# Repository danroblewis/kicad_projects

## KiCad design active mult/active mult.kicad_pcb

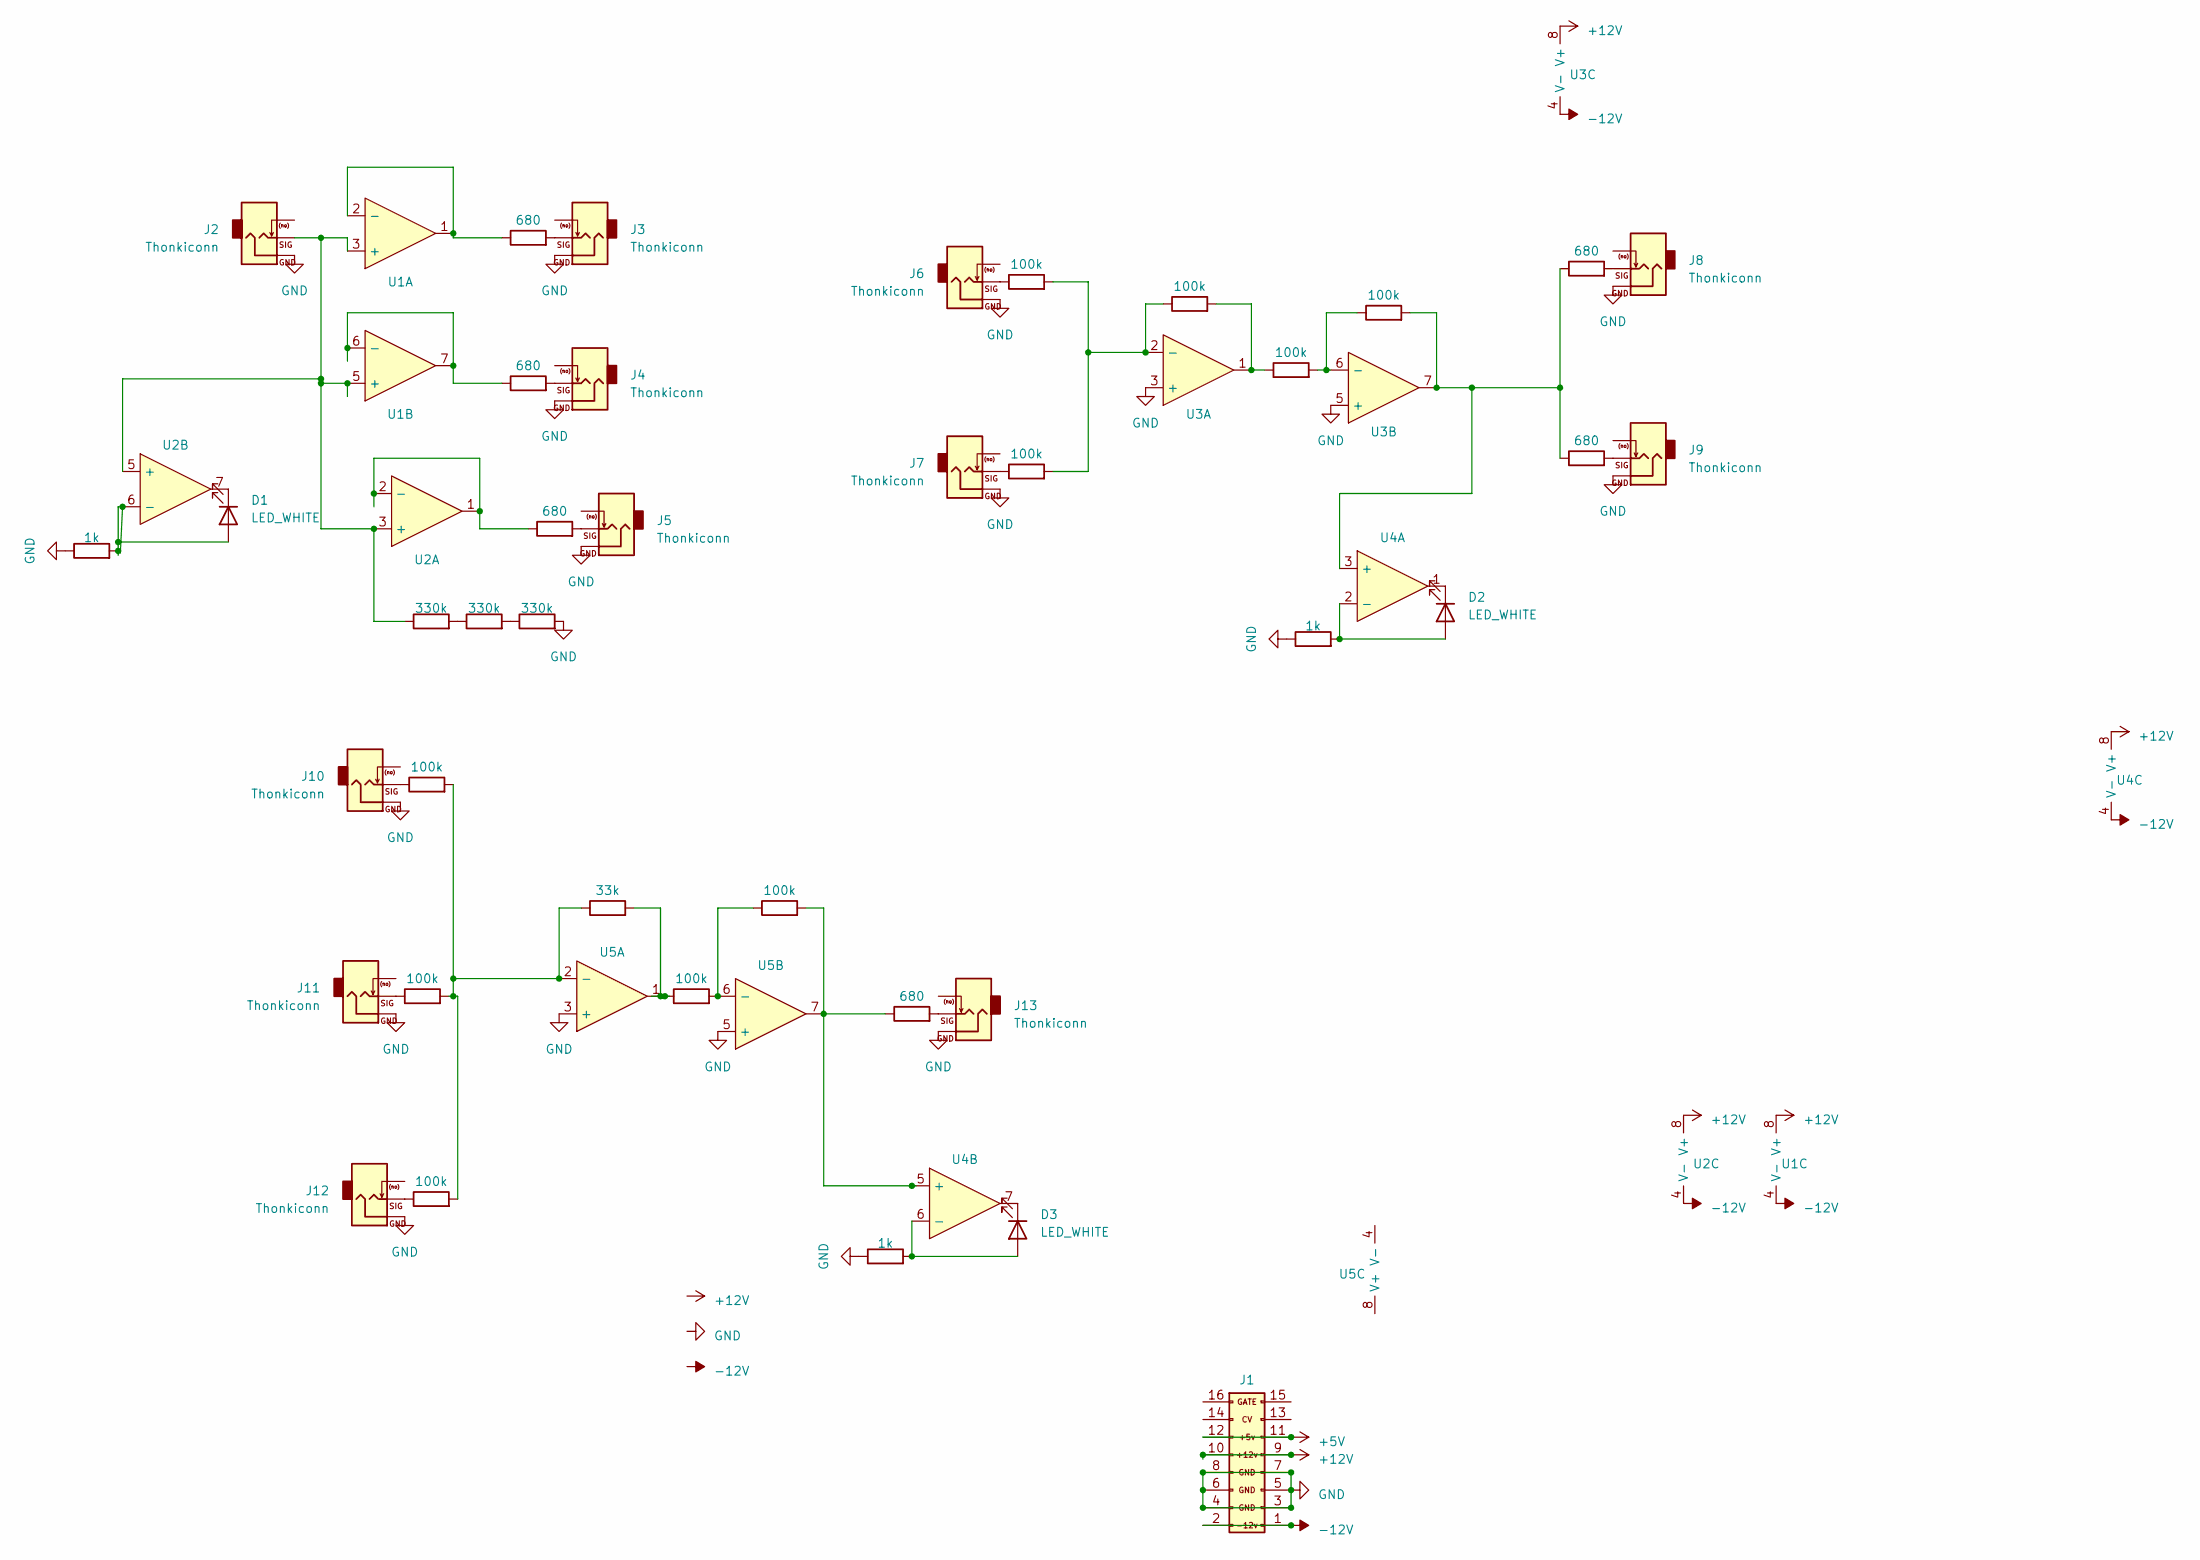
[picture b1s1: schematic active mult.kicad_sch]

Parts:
D1, D2, D3: LED_WHITE; LED_0603_1608Metric; LCSC C2290
J1: EuroPower16; IDC-Header_2x08_P2.54mm_Vertical_SMD; lcsc C383608
J2, J3, J4, J5, J6, J7, J8, J9, J10, J11, J12, J13: Thonkiconn; Jack_3.5mm_QingPu_WQP-PJ398SM_Vertical_CircularHoles
R1, R13, R21: 1k; R_0603_1608Metric; LCSC C21190
R2, R5, R6, R8, R9, R20: 680; R_0603_1608Metric; LCSC C23228
R3, R4, R10, R11, R12, R14, R15, R16, R18, R19: 100k; R_0603_1608Metric; LCSC C25803
R17: 33k; R_0603_1608Metric; LCSC C4216
R22, R23, R24: 330k; R_0603_1608Metric; LCSC C23137
U1, U2, U3, U4, U5: TL072; SOIC-8_3.9x4.9mm_P1.27mm; LCSC C6961

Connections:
+5V: J1.11 (+5v_R), J1.12 (+5v_L)
+12V: J1.9 (+12V_R), J1.10 (+12V_L), U1.8 (V+), U2.8 (V+), U3.8 (V+), U4.8 (V+)
-12V: J1.1 (-12v_R), J1.2 (-12v_L), U1.4 (V-), U2.4 (V-), U3.4 (V-), U4.4 (V-)
GND: J1.3 (GND), J1.4 (GND), J1.5 (GND_R3), J1.6 (GND_L3), J1.7 (GND_R2), J1.8 (GND_L2), J2.S, J3.S, J4.S, J5.S, J6.S, J7.S, J8.S, J9.S, J10.S, J11.S, J12.S, J13.S, R1.1, R13.1, R21.1, R24.2, U3.3 (+), U3.5 (+), U5.3 (+), U5.5 (+)
unnamed: D1.2 (A), R1.2, U2.6 (-)
unnamed: D1.1 (K), U2.7
unnamed: D2.2 (A), R13.2, U4.2 (-)
unnamed: D2.1 (K), U4.1
unnamed: D3.2 (A), R21.2, U4.6 (-)
unnamed: D3.1 (K), U4.7
unnamed: J3.T, R2.2
unnamed: J4.T, R6.2
unnamed: J5.T, R8.2
unnamed: J6.T, R3.1
unnamed: J7.T, R4.1
unnamed: J8.T, R5.2
unnamed: J9.T, R9.2
unnamed: J10.T, R14.1
unnamed: J11.T, R15.1
unnamed: J12.T, R16.1
unnamed: J13.T, R20.2
unnamed: R10.2, R11.1, U3.1
unnamed: R17.2, R18.1, U5.1
unnamed: R22.2, R23.1
unnamed: R23.2, R24.1
unnamed: J2.T, R22.1, U1.3 (+), U1.5 (+), U2.3 (+), U2.5 (+)
unnamed: R2.1, U1.1, U1.2 (-)
unnamed: R6.1, U1.6 (-), U1.7
unnamed: R8.1, U2.1, U2.2 (-)
unnamed: R3.2, R4.2, R10.1, U3.2 (-)
unnamed: R11.2, R12.1, U3.6 (-)
unnamed: R5.1, R9.1, R12.2, U3.7, U4.3 (+)
unnamed: R19.2, R20.1, U4.5 (+), U5.7
unnamed: R14.2, R15.2, R16.2, R17.1, U5.2 (-)
unnamed: R18.2, R19.1, U5.6 (-)

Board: 2 copper layers, 44 parts (12 on the bottom side), 35 nets, no tracks yet.

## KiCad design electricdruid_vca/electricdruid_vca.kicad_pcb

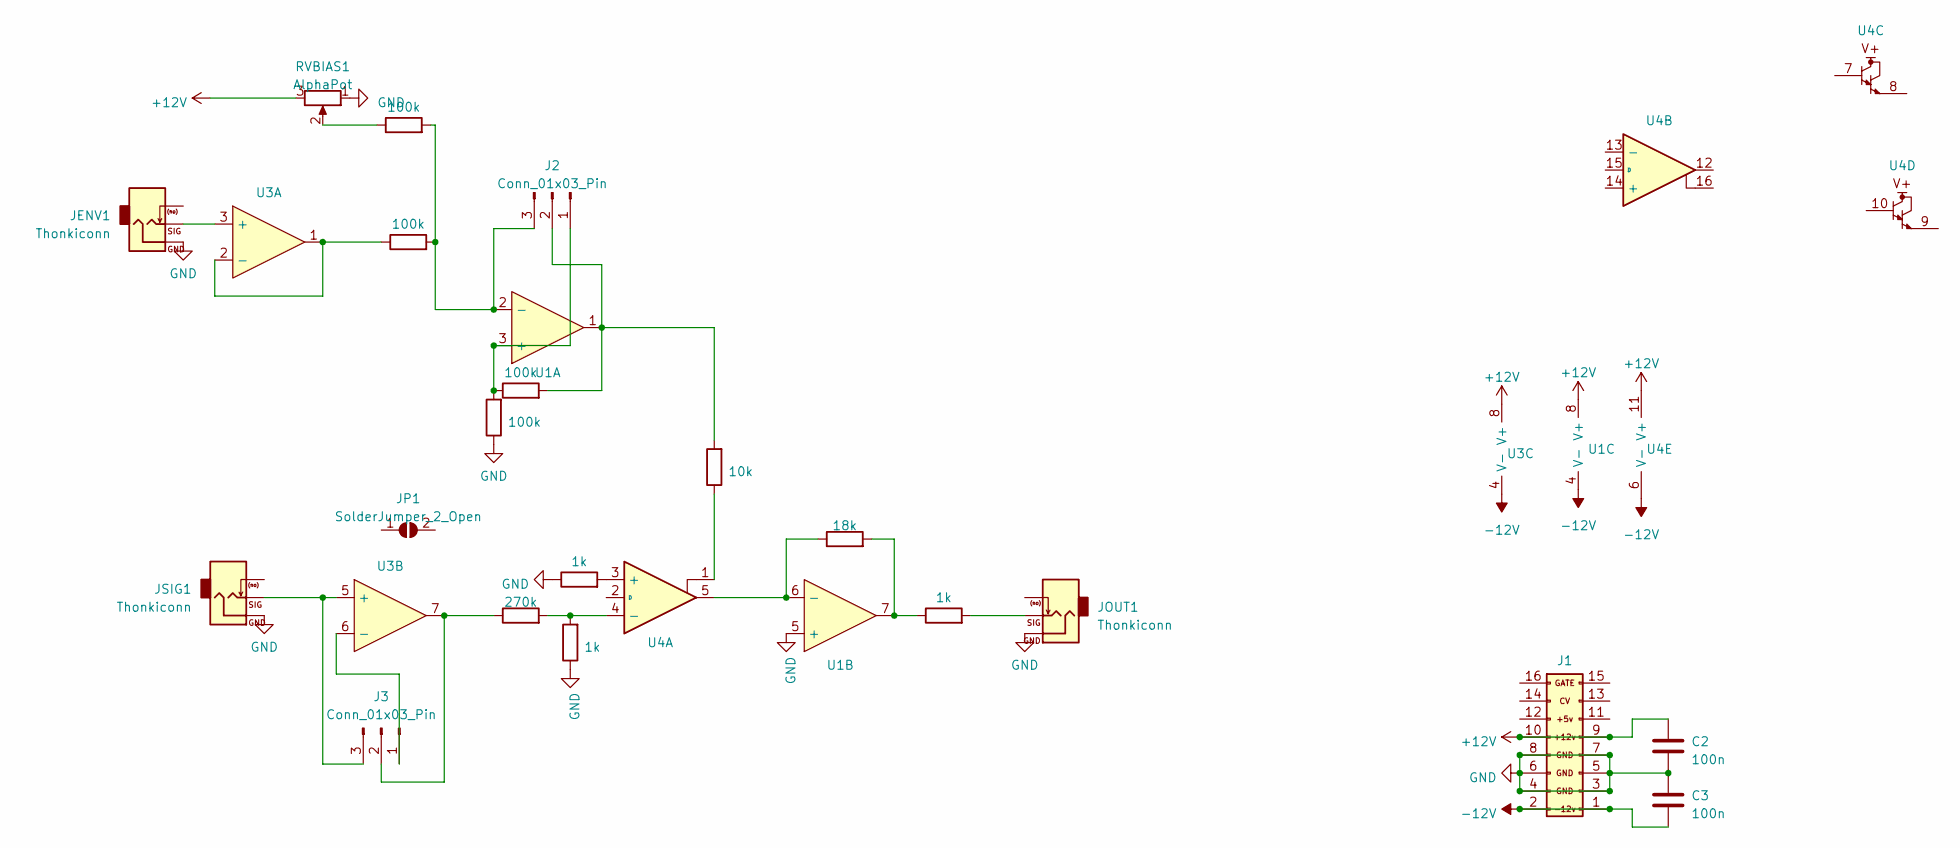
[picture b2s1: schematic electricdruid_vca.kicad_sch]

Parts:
C2, C3: 100n; C_0603_1608Metric; LCSC C14663
J1: EuroPower16; IDC-Header_2x08_P2.54mm_Vertical_SMD; lcsc C383608
J2, J3: Conn_01x03_Pin; PinHeader_1x03_P2.54mm_Vertical
JENV1: Thonkiconn; Jack_3.5mm_QingPu_WQP-PJ398SM_Vertical_CircularHoles
JOUT1: Thonkiconn; Jack_3.5mm_QingPu_WQP-PJ398SM_Vertical_CircularHoles
JP1: SolderJumper_2_Open; SolderJumper-2_P1.3mm_Open_TrianglePad1.0x1.5mm
JSIG1: Thonkiconn; Jack_3.5mm_QingPu_WQP-PJ398SM_Vertical_CircularHoles
R1: 10k; R_0603_1608Metric; lcsc C73809
R2, R7, R12: 1k; R_0603_1608Metric; LCSC C21190
R5, R6, R9, R10: 100k; R_0603_1608Metric; LCSC C25803
R8: 270k; R_0603_1608Metric; LCSC C103491
R11: 18k; R_0603_1608Metric; lcsc C25810
RVBIAS1: AlphaPot; Potentiometer_Alpha_RD901F-40-00D_Single_Vertical
U1, U3: TL072; SOIC-8_3.9x4.9mm_P1.27mm; LCSC C6961
U4: XL13700; SOP-16_3.9x9.9mm_P1.27mm; LCSC C521166

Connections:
+12V: C2.1, J1.9 (+12V_R), J1.10 (+12V_L), RVBIAS1.3, U1.8 (V+), U3.8 (V+), U4.11 (V+)
-12V: C3.2, J1.1 (-12v_R), J1.2 (-12v_L), U1.4 (V-), U3.4 (V-), U4.6 (V-)
GND: C2.2, C3.1, J1.3 (GND), J1.4 (GND), J1.5 (GND_R3), J1.6 (GND_L3), J1.7 (GND_R2), J1.8 (GND_L2), JENV1.S, JOUT1.S, JSIG1.S, R2.1, R7.1, R10.1, RVBIAS1.1, U1.5 (+)
unnamed: J2.1, R9.1, R10.2, U1.3 (+)
unnamed: J2.2, R1.2, R9.2, U1.1
unnamed: J2.3, R5.2, R6.2, U1.2 (-)
unnamed: J3.1, U3.6 (-)
unnamed: J3.2, R8.1, U3.7
unnamed: J3.3, JSIG1.T, U3.5 (+)
unnamed: JOUT1.T, R12.2
unnamed: R1.1, U4.1
unnamed: R5.1, RVBIAS1.2
unnamed: R11.2, R12.1, U1.7
unnamed: R11.1, U1.6 (-), U4.5
unnamed: JENV1.T, U3.3 (+)
unnamed: R6.1, U3.1, U3.2 (-)
unnamed: R2.2, U4.3 (+)
unnamed: R7.2, R8.2, U4.4 (-)

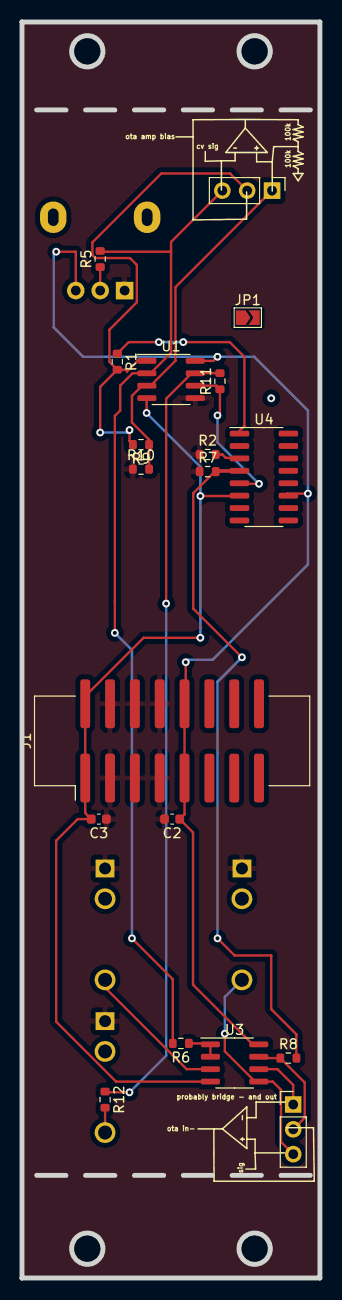
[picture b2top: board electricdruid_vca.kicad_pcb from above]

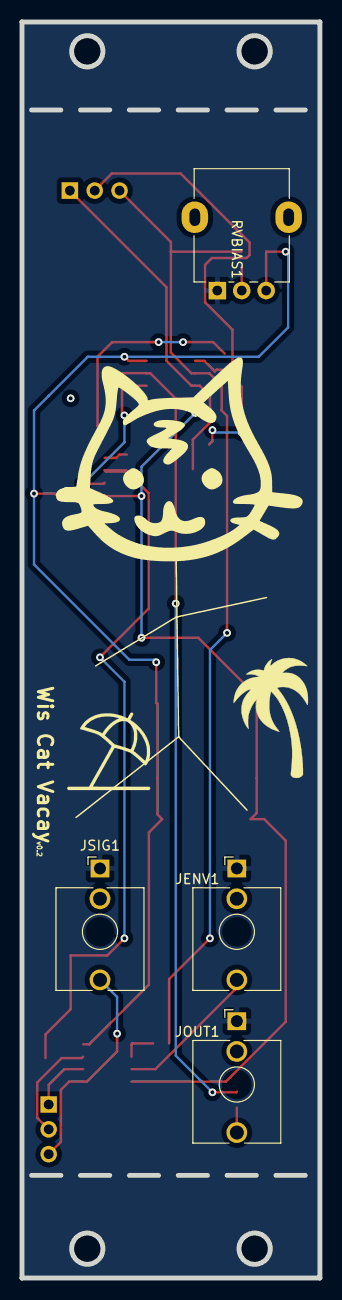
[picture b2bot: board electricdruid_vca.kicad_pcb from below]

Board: 2 copper layers, 30.5 x 128.5 mm, 23 parts (4 on the bottom side), 18 nets.

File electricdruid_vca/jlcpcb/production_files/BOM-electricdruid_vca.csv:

Comment,Designator,Footprint,LCSC
270k,R8,R_0603_1608Metric,C103491
100n,"C2,C3",C_0603_1608Metric,C14663
1k,"R12,R2,R7",R_0603_1608Metric,C21190
100k,"R10,R5,R6,R9",R_0603_1608Metric,C25803
18k,R11,R_0603_1608Metric,C25810
EuroPower16,J1,IDC-Header_2x08_P2.54mm_Vertical_SMD,C383608
XL13700,U4,SOP-16_3.9x9.9mm_P1.27mm,C521166
TL072,"U1,U3",SOIC-8_3.9x4.9mm_P1.27mm,C67473
10k,R1,R_0603_1608Metric,C73809

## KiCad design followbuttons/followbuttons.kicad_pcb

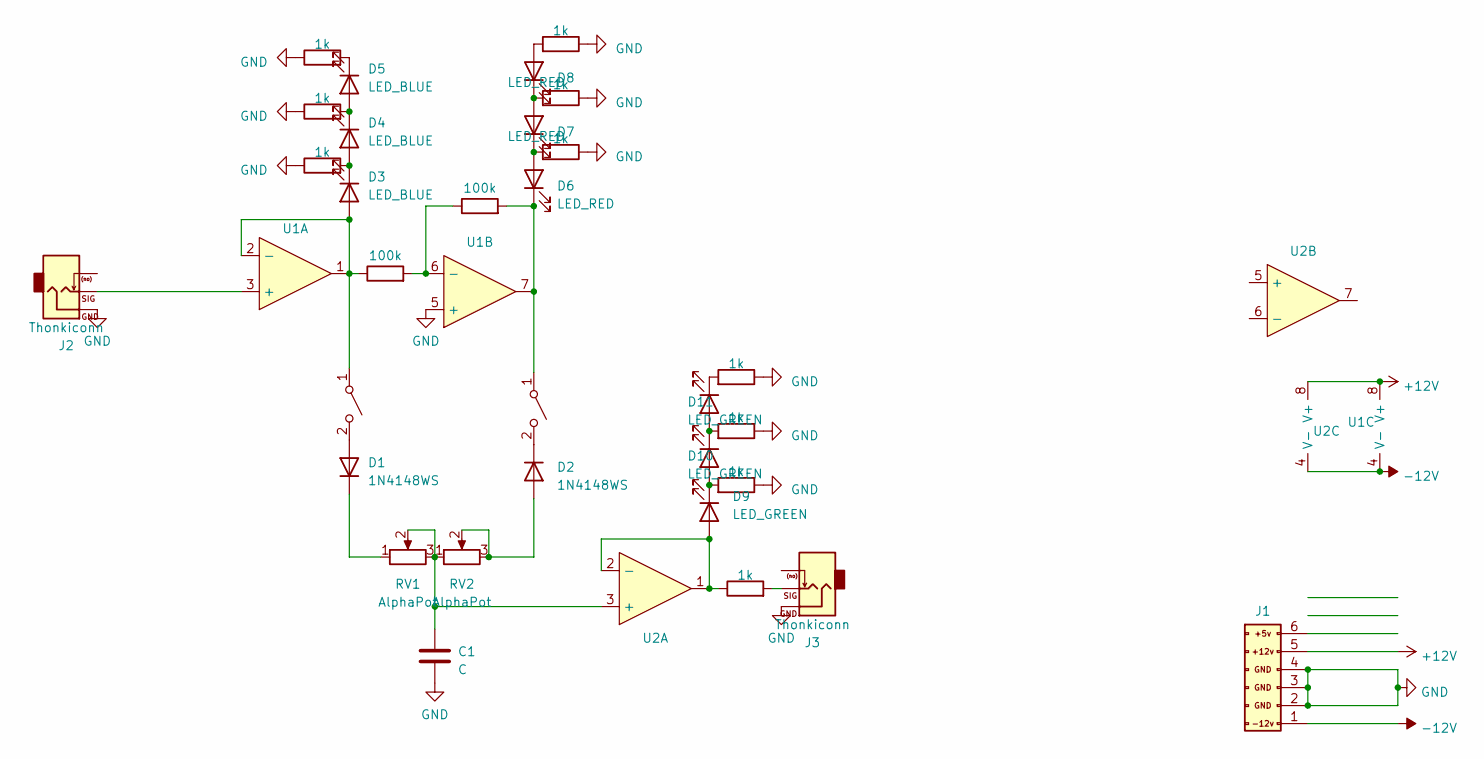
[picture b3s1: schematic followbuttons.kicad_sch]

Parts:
C1: C; CP_Radial_D5.0mm_P2.50mm
D1, D2: 1N4148WS; D_SOD-323; LCSC C2128
D3, D4, D5: LED_BLUE; LED_0603_1608Metric; LCSC C72041
D6, D7, D8: LED_RED; LED_0603_1608Metric; LCSC C2296
D9, D10, D11: LED_GREEN; LED_0603_1608Metric; LCSC C72043
J1: EuroPower16; PinHeader_1x07_P2.54mm_Vertical; lcsc C383608
J2, J3: Thonkiconn; Jack_3.5mm_QingPu_WQP-PJ398SM_Vertical_CircularHoles
R1, R2: 100k; R_0603_1608Metric; LCSC C25803
R3, R4, R5, R6, R7, R8, R9, R10, R11, R12: 1k; R_0603_1608Metric; LCSC C21190
RV1, RV2: AlphaPot; Potentiometer_Alpha_RD901F-40-00D_Single_Vertical
SW1, SW2: SW_SPST; SW_SPST_PTS645; lcsc C294565
U1, U2: TL072; SOIC-8_3.9x4.9mm_P1.27mm; LCSC C67473

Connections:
+12V: J1.5 (GND_R3), U1.8 (V+), U2.8 (V+)
-12V: J1.1 (-12v_R), U1.4 (V-), U2.4 (V-)
GND: C1.2, J1.2 (-12v_L), J1.3 (GND), J1.4 (GND), J2.S, J3.S, R4.1, R5.1, R6.1, R7.1, R8.1, R9.1, R10.1, R11.1, R12.1, U1.5 (+)
unnamed: D1.2 (A), SW1.2 (B)
unnamed: D1.1 (K), RV1.1
unnamed: D2.2 (A), RV2.2, RV2.3
unnamed: D2.1 (K), SW2.2 (B)
unnamed: D3.2 (A), R2.1, SW1.1 (A), U1.1, U1.2 (-)
unnamed: D3.1 (K), D4.2 (A), R4.2
unnamed: D4.1 (K), D5.2 (A), R5.2
unnamed: D5.1 (K), R6.2
unnamed: D6.2 (A), D7.1 (K), R9.2
unnamed: D6.1 (K), R1.2, SW2.1 (A), U1.7
unnamed: D7.2 (A), D8.1 (K), R8.2
unnamed: D8.2 (A), R7.2
unnamed: D9.2 (A), R3.1, U2.1, U2.2 (-)
unnamed: D9.1 (K), D10.2 (A), R12.2
unnamed: D10.1 (K), D11.2 (A), R11.2
unnamed: D11.1 (K), R10.2
unnamed: J3.T, R3.2
unnamed: J2.T, U1.3 (+)
unnamed: R1.1, R2.2, U1.6 (-)
unnamed: C1.1, RV1.2, RV1.3, RV2.1, U2.3 (+)

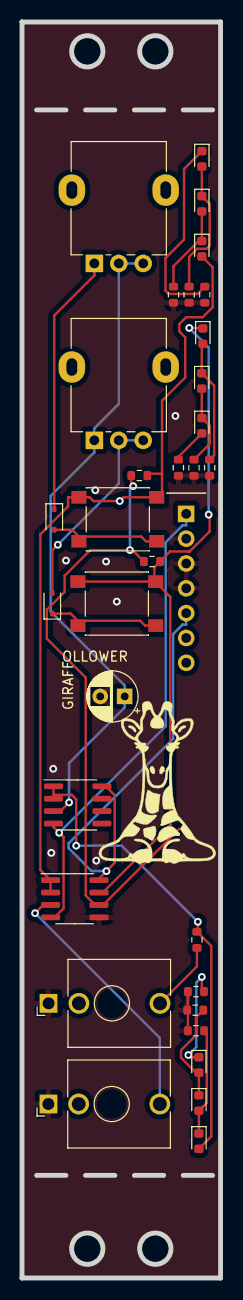
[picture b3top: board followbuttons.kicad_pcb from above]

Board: 2 copper layers, 20.3 x 128.5 mm, 33 parts (1 on the bottom side), 23 nets.

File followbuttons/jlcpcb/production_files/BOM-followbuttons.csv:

Comment,Designator,Footprint,LCSC
1k,"R10,R11,R12,R3,R4,R5,R6,R7,R8,R9",R_0603_1608Metric,C21190
1N4148WS,"D1,D2",D_SOD-323,C2128
LED_RED,"D6,D7,D8",LED_0603_1608Metric,C2296
100k,"R1,R2",R_0603_1608Metric,C25803
SW_SPST,"SW1,SW2",SW_SPST_PTS645,C294565
TL072,"U1,U2",SOIC-8_3.9x4.9mm_P1.27mm,C67473
LED_BLUE,"D3,D4,D5",LED_0603_1608Metric,C72041
LED_GREEN,"D10,D11,D9",LED_0603_1608Metric,C72043

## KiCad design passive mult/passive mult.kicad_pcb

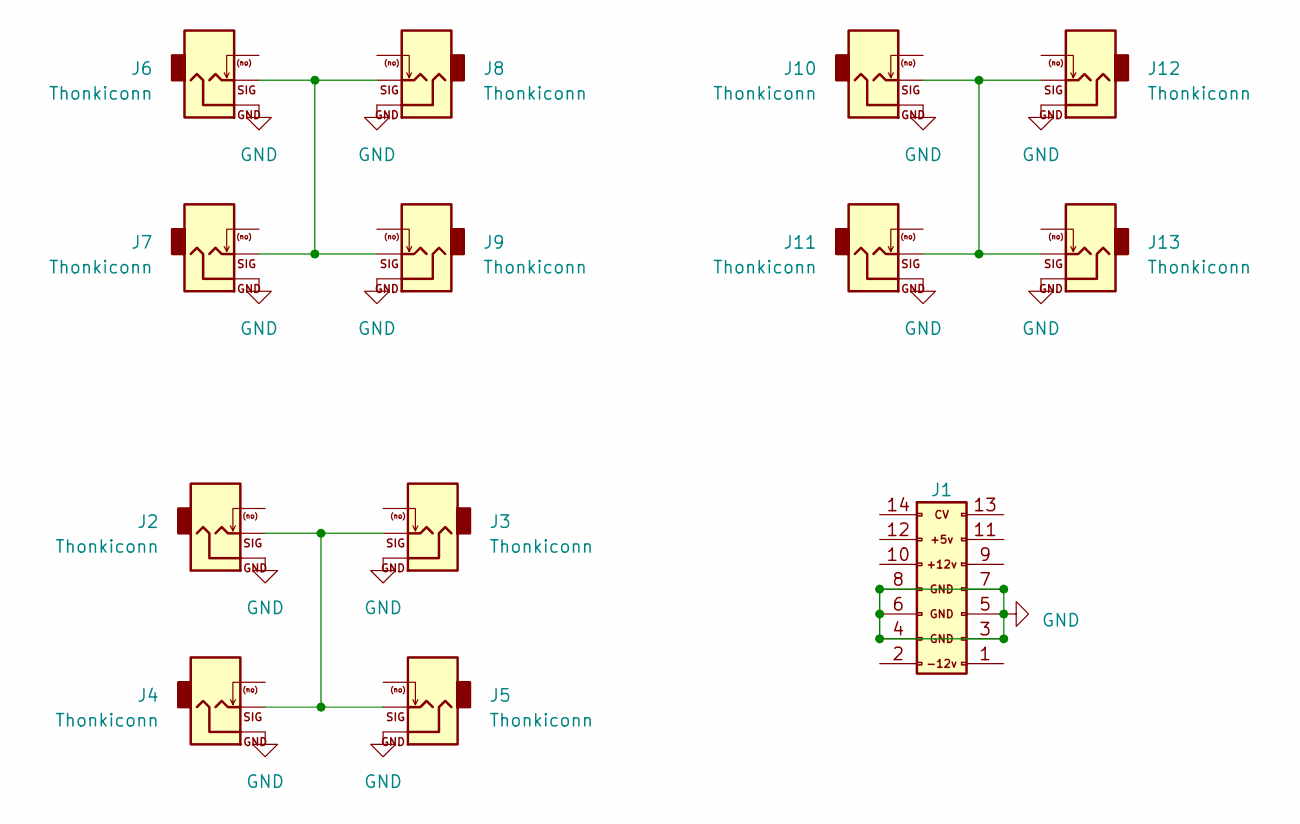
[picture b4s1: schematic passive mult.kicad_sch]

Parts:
J1: EuroPower16; PinHeader_2x07_P2.54mm_Vertical_SMD; lcsc C2884016
J2, J3, J4, J5, J6, J7, J8, J9, J10, J11, J12, J13: Thonkiconn; Jack_3.5mm_QingPu_WQP-PJ398SM_Vertical_CircularHoles

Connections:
GND: J1.3 (GND), J1.4 (GND), J1.5 (GND_R3), J1.6 (GND_L3), J1.7 (GND_R2), J1.8 (GND_L2), J2.S, J3.S, J4.S, J5.S, J6.S, J7.S, J8.S, J9.S, J10.S, J11.S, J12.S, J13.S
unnamed: J2.T, J3.T, J4.T, J5.T
unnamed: J6.T, J7.T, J8.T, J9.T
unnamed: J10.T, J11.T, J12.T, J13.T

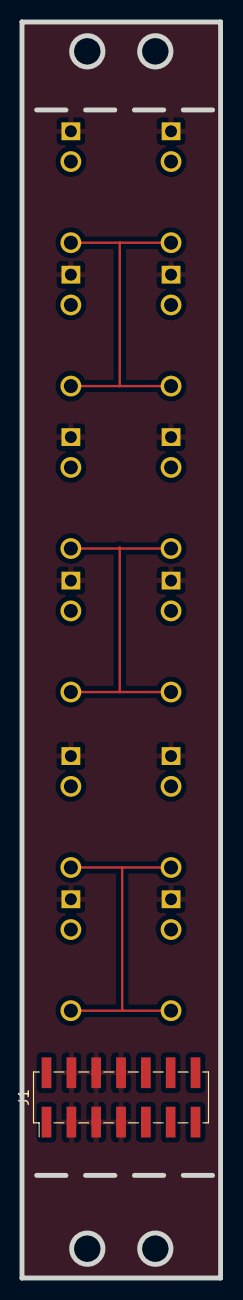
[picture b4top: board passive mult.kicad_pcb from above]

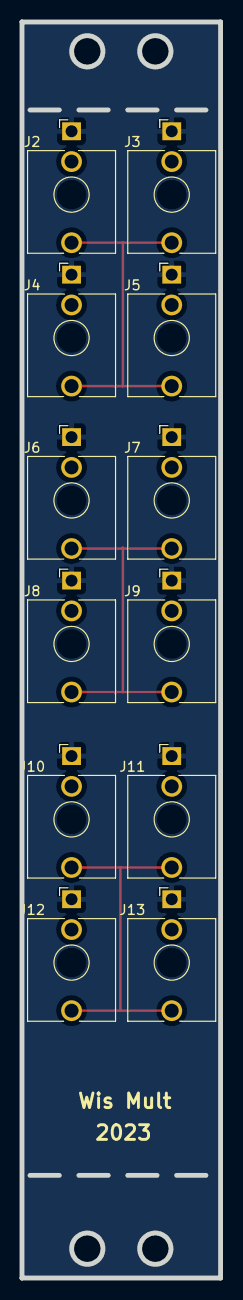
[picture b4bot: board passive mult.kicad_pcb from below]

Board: 2 copper layers, 20.3 x 128.5 mm, 13 parts (12 on the bottom side), 4 nets.

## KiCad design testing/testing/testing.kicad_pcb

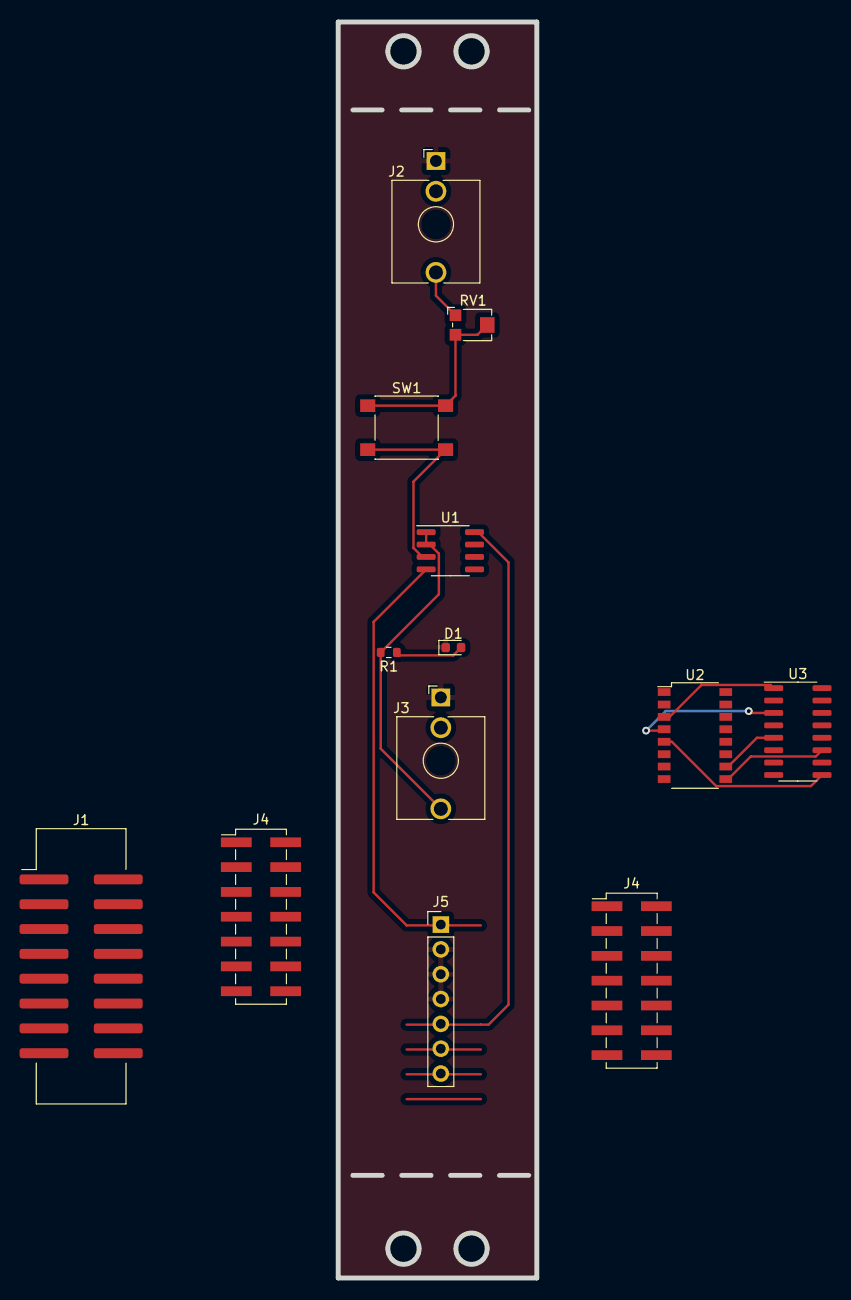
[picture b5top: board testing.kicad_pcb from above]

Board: 2 copper layers, 20.3 x 128.5 mm, 13 parts (0 on the bottom side), 15 nets.

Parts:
D1: LED_WHITE; LED_0603_1608Metric
J1: EuroPower16; IDC-Header_2x08_P2.54mm_Vertical_SMD
J2, J3: Thonkiconn; Jack_3.5mm_QingPu_WQP-PJ398SM_Vertical_CircularHoles
J4, J4#2: EuroPower16; PinHeader_2x07_P2.54mm_Vertical_SMD
J5: EuroPower16; PinHeader_1x07_P2.54mm_Vertical
R1: 22k; R_0603_1608Metric
RV1: R_Potentiometer_Trim_US; Potentiometer_Bourns_TC33X_Vertical
SW1: SW_SPST; SW_SPST_PTS645
U1: TL072; SOIC-8_3.9x4.9mm_P1.27mm
U2: CD4017BM; SOP-16_4.4x10.4mm_P1.27mm
U3: CD40106; SOIC-16_3.9x9.9mm_P1.27mm

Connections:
+5V: J4.11 (+5v_R), J4.12 (+5v_L), J5.6 (GND_L3)
+12V: J4.9 (+12V_R), J4.10 (+12V_L), J5.5 (GND_R3), U1.8 (V+), U3.14 (VDD)
-12V: J4.1 (-12v_R), J4.2 (-12v_L), J5.1 (-12v_R), U1.4 (V-)
GND: D1.1 (K), J2.S, J3.S, J4.3 (GND), J4.4 (GND), J4.5 (GND_R3), J4.6 (GND_L3), J4.7 (GND_R2), J4.8 (GND_L2), J5.2 (-12v_L), J5.3 (GND), J5.4 (GND), U3.7 (VSS)
unnamed: D1.2 (A), R1.1
unnamed: J2.T, RV1.1
unnamed: J4.13 (CV_R), J4.14 (CV_L)
unnamed: RV1.2, RV1.3, SW1.1 (A)
unnamed: SW1.2 (B), U1.3 (+)
unnamed: J3.T, R1.2, U1.1, U1.2 (-)
unnamed: U2.3 (Q0), U3.1
unnamed: U2.4 (Q2), U3.3
unnamed: U2.10 (Q4), U3.5
unnamed: U2.5 (Q6), U3.9
unnamed: U2.9 (Q8), U3.11

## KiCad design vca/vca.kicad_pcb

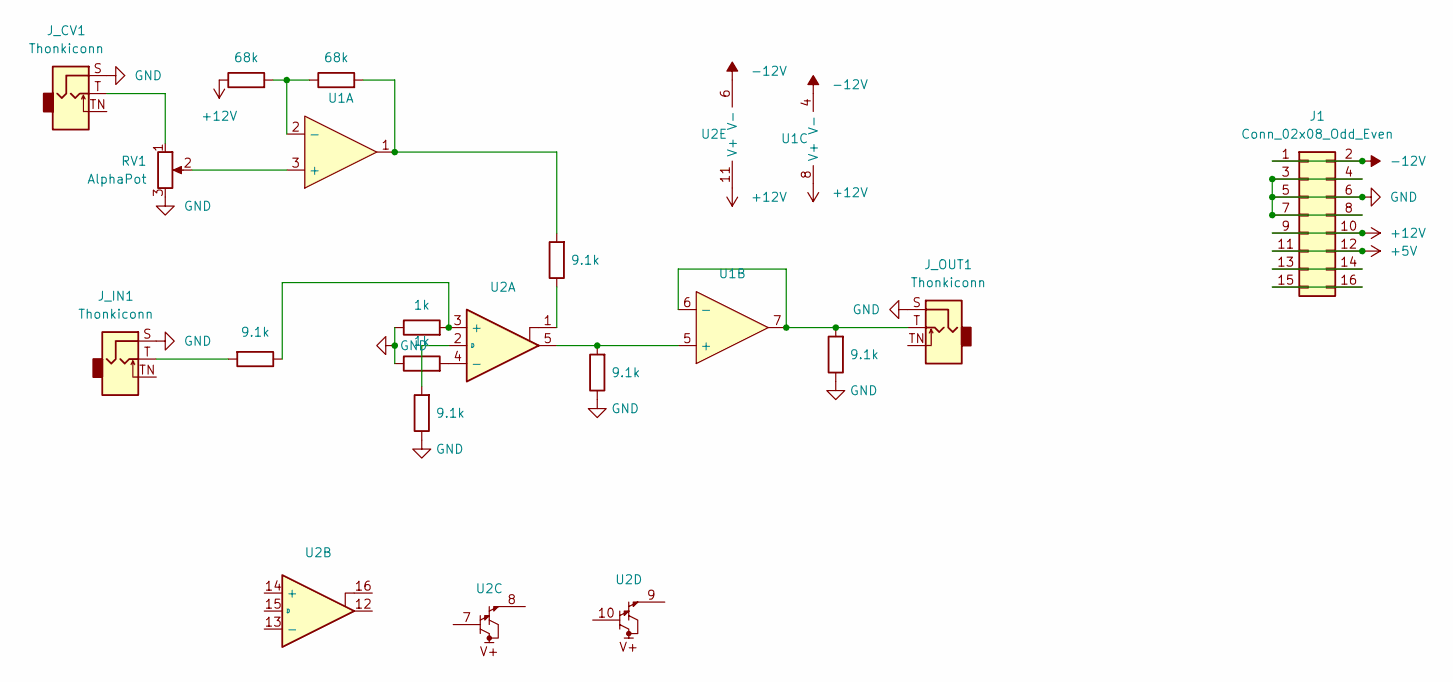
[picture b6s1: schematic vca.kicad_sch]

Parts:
J1: Conn_02x08_Odd_Even; IDC-Header_2x08_P2.54mm_Vertical
J_CV1: Thonkiconn; Jack_3.5mm_QingPu_WQP-PJ398SM_Vertical_CircularHoles
J_IN1: Thonkiconn; Jack_3.5mm_QingPu_WQP-PJ398SM_Vertical_CircularHoles
J_OUT1: Thonkiconn; Jack_3.5mm_QingPu_WQP-PJ398SM_Vertical_CircularHoles
R1, R6, R7, R8, R9: 9.1k; R_0603_1608Metric; LCSC C23260
R2, R3: 68k; R_0603_1608Metric; LCSC C23231
R4, R5: 1k; R_0603_1608Metric; LCSC C21190
RV1: AlphaPot; Potentiometer_Alpha_RD901F-40-00D_Single_Vertical
U1: TL072; SOIC-8_3.9x4.9mm_P1.27mm; LCSC C6961
U2: LM13700; SOIC-16_3.9x9.9mm_P1.27mm; LCSC C174050

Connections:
+5V: J1.11, J1.12
+12V: J1.9, J1.10, R2.1, U1.8 (V+), U2.11 (V+)
-12V: J1.1, J1.2, U1.4 (V-), U2.6 (V-)
GND: J1.3, J1.4, J1.5, J1.6, J1.7, J1.8, J_CV1.S, J_IN1.S, J_OUT1.S, R4.1, R5.1, R6.1, R8.1, R9.1, RV1.3
unnamed: J1.13, J1.14
unnamed: J1.15, J1.16
unnamed: J_CV1.T, RV1.1
unnamed: J_IN1.T, R1.2
unnamed: J_OUT1.T, R9.2, U1.6 (-), U1.7
unnamed: R1.1, R4.2, U2.3 (+)
unnamed: R2.2, R3.1, U1.2 (-)
unnamed: R3.2, R7.2, U1.1
unnamed: R5.2, U2.4 (-)
unnamed: R6.2, U2.2 (D)
unnamed: R7.1, U2.1
unnamed: RV1.2, U1.3 (+)
unnamed: R8.2, U1.5 (+), U2.5

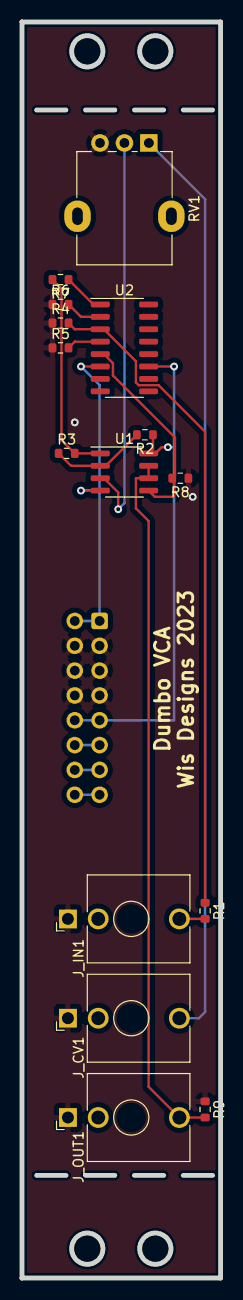
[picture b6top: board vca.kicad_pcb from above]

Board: 2 copper layers, 20.3 x 128.5 mm, 16 parts (1 on the bottom side), 17 nets.

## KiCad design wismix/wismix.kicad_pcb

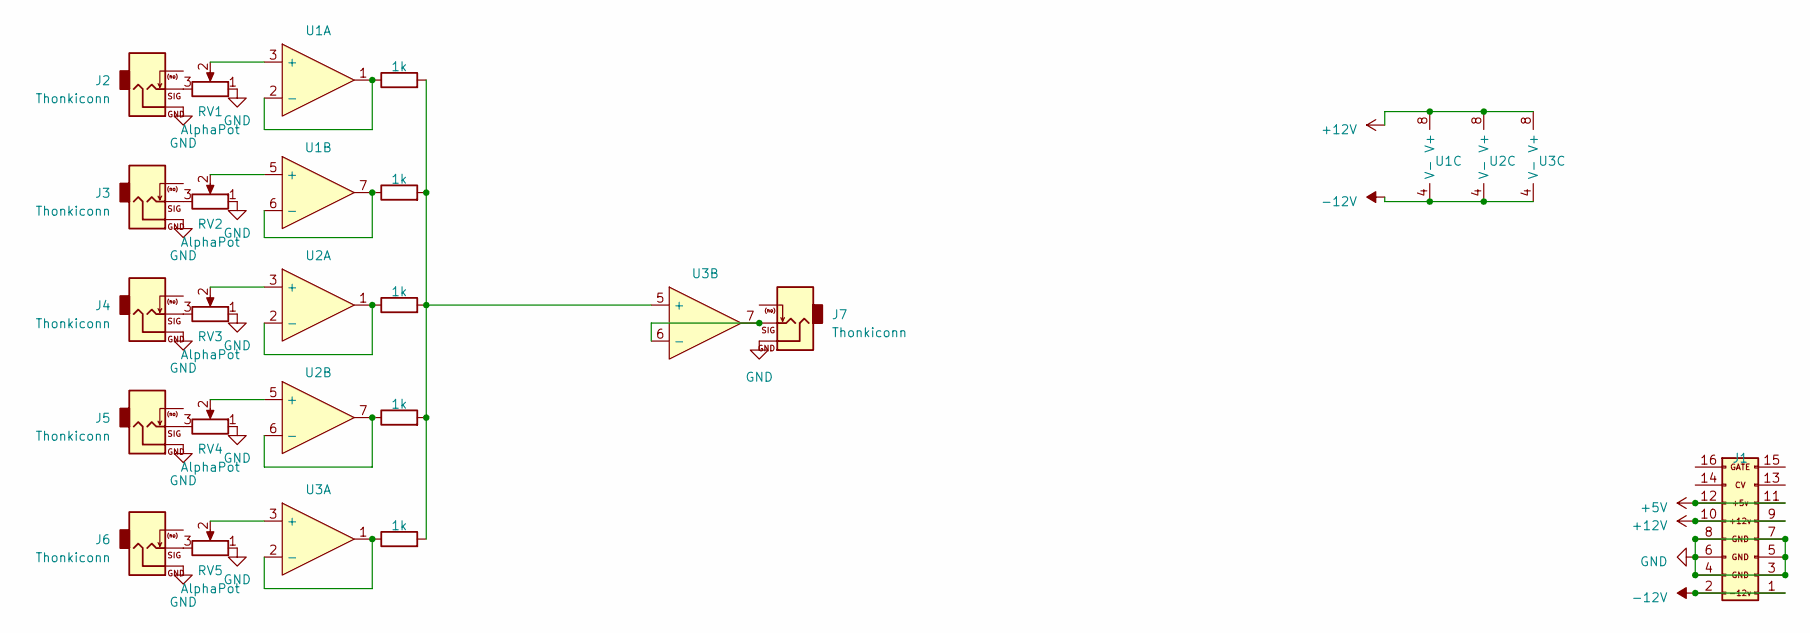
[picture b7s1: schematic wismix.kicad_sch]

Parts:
J1: EuroPower16; IDC-Header_2x08_P2.54mm_Vertical_SMD; lcsc C383608
J2, J3, J4, J5, J6, J7: Thonkiconn; Jack_3.5mm_QingPu_WQP-PJ398SM_Vertical_CircularHoles
R1, R2, R3, R4, R5: 1k; R_0603_1608Metric; LCSC C21190
RV1, RV2, RV3, RV4, RV5: AlphaPot; Potentiometer_Alpha_RD901F-40-00D_Single_Vertical
U1, U2, U3: TL072; SOIC-8_3.9x4.9mm_P1.27mm; LCSC C6961

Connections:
+5V: J1.11 (+5v_R), J1.12 (+5v_L)
+12V: J1.9 (+12V_R), J1.10 (+12V_L), U1.8 (V+), U2.8 (V+), U3.8 (V+)
-12V: J1.1 (-12v_R), J1.2 (-12v_L), U1.4 (V-), U2.4 (V-), U3.4 (V-)
GND: J1.3 (GND), J1.4 (GND), J1.5 (GND_R3), J1.6 (GND_L3), J1.7 (GND_R2), J1.8 (GND_L2), J2.S, J3.S, J4.S, J5.S, J6.S, J7.S, RV1.1, RV2.1, RV3.1, RV4.1, RV5.1
unnamed: J2.T, RV1.3
unnamed: J3.T, RV2.3
unnamed: J4.T, RV3.3
unnamed: J5.T, RV4.3
unnamed: J6.T, RV5.3
unnamed: RV1.2, U1.3 (+)
unnamed: R1.1, U1.1, U1.2 (-)
unnamed: RV2.2, U1.5 (+)
unnamed: R2.1, U1.6 (-), U1.7
unnamed: RV3.2, U2.3 (+)
unnamed: R3.1, U2.1, U2.2 (-)
unnamed: RV4.2, U2.5 (+)
unnamed: R4.1, U2.6 (-), U2.7
unnamed: RV5.2, U3.3 (+)
unnamed: R5.1, U3.1, U3.2 (-)
unnamed: R1.2, R2.2, R3.2, R4.2, R5.2, U3.5 (+)
unnamed: J7.T, U3.6 (-), U3.7

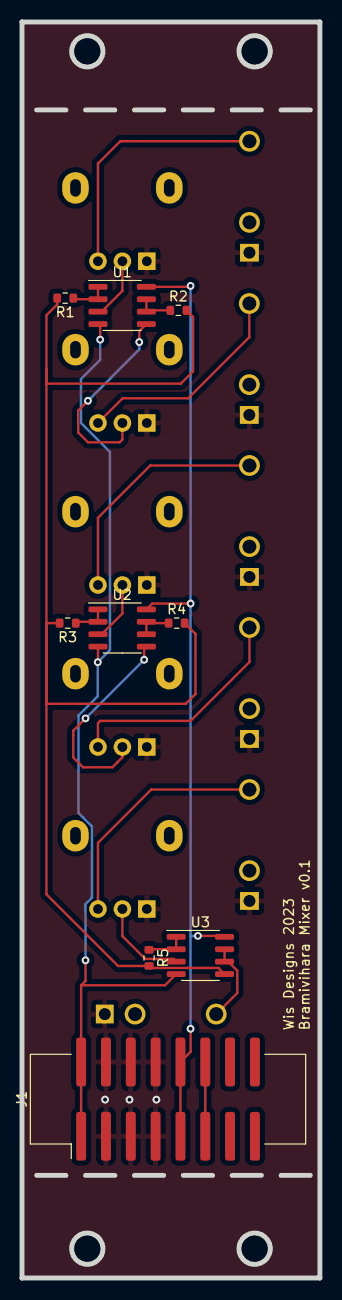
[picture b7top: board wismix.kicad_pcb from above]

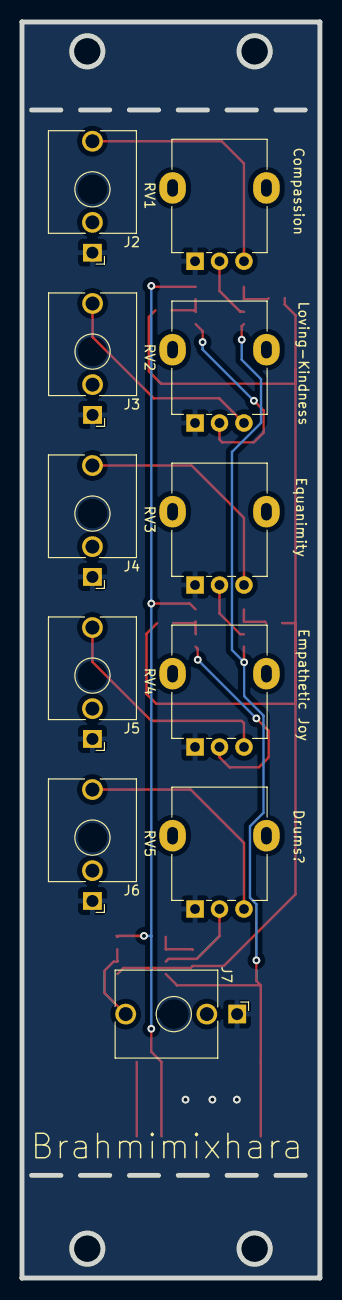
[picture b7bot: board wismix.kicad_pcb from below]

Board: 2 copper layers, 30.5 x 128.5 mm, 20 parts (11 on the bottom side), 21 nets.

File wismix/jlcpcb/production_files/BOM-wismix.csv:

Comment,Designator,Footprint,LCSC
1k,"R1,R2,R3,R4,R5",R_0603_1608Metric,C21190
EuroPower16,J1,IDC-Header_2x08_P2.54mm_Vertical_SMD,C383608
TL072,"U1,U2,U3",SOIC-8_3.9x4.9mm_P1.27mm,C6961
